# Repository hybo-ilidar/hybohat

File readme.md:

# Hybohat Development Board 

## Update R3

Correction was made for Arduino Nano module.
ESP32 module was adjusted for use with male pin header modules.

## Introduction

The Hybohat module was designed as a simple, passive way to interconnect
the User I/O connector of the iLidar to a variety of common development
boards.  These are:

* STM32F4 Discovery
* Arduino Uno & Leonardo
* STM32F429ZI Nucleo
* ESP32
* Raspberry Pi & Pi Zero
* Arduino Nano (and STM32F103 Nano form-factor)

## Concept

The board can be envisioned as a large cross-bar switch with each
dev board's I/O ports conected to a bus.  In case a development board
has multiple ports of the same time, the desired port is selected with 
jumpers in the three vertical columns labeled 

* `SPI SEL JUMPERS` (JP4NN1, JP4DD1)
* `I2C SEL JUMPERS` (JP2NN1, JP2DD1)
* `ASYNC SEL JUMPERS` (JP3NN1, JP3DD1, JP2EE1)

One end of this bus is connected to iLidar's User I/O
connector by the jumper block labeled: `I/O MODE SELECT (JP6)`
Note that only one mode can be operational at a time.

The other end of the bus is terminated in four connectors which can be
used to probe and monitor the I/O:

* `I2C` (J2)
* `SPI` (J3)
* `ASYNC` (J4)
* `TRIG` (J5)

## Development Boards

IMPORTANT: ONLY ONE DEVELOPMENT BOARD MAY BE CONNECTED AT ONE TIME

* Module A2, ESP32
  - XA2J2
  - XA2J3

* Module A3, Raspberry Pi & Pi Zero
  - XA3GPIO1

* Module A4, Arduino Nano
  - XA4J1 
  - XA4J2 

* Module A5, STM32F4 Discovery 
  - XA5P1
  - XA5P2

* Module A6, STM32F429ZI Nucleo Arduino Uno & Leonardo
  - XA6CN7
  - XA6CN8
  - XA6CN9
  - XA6CN10

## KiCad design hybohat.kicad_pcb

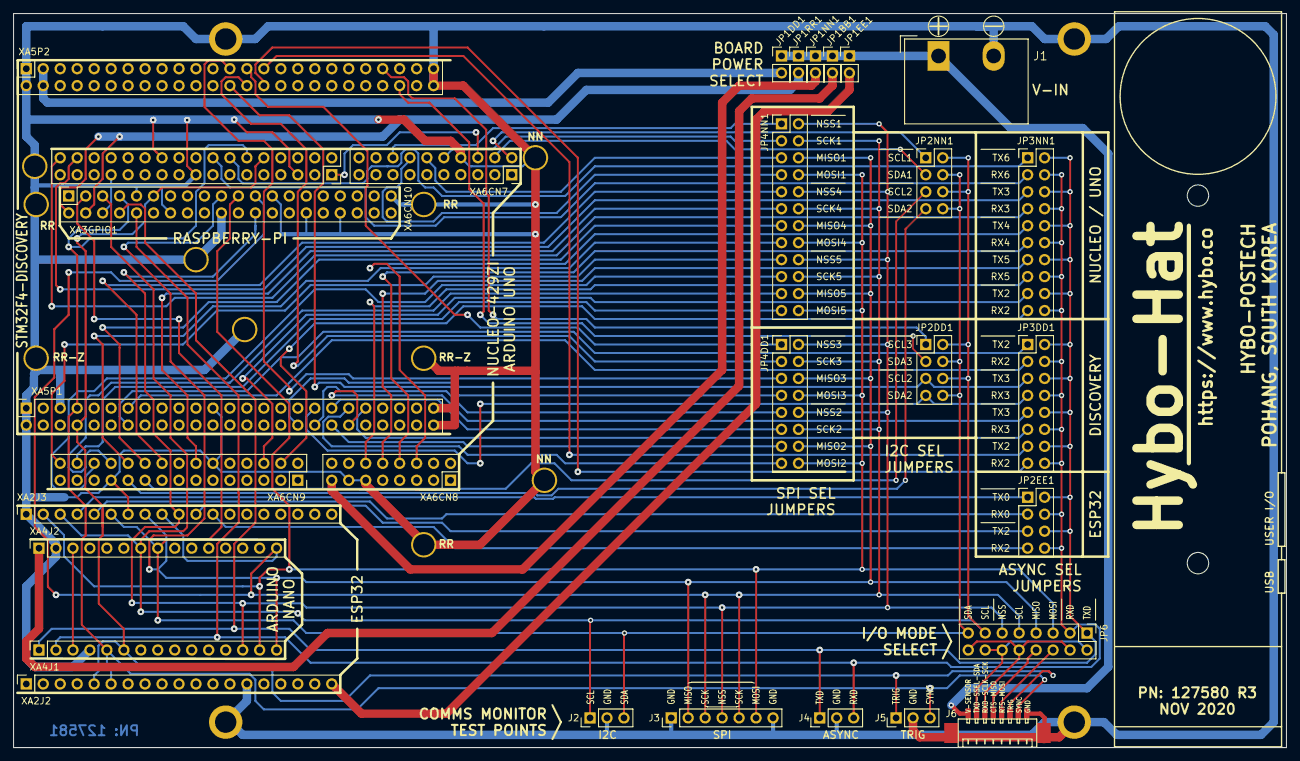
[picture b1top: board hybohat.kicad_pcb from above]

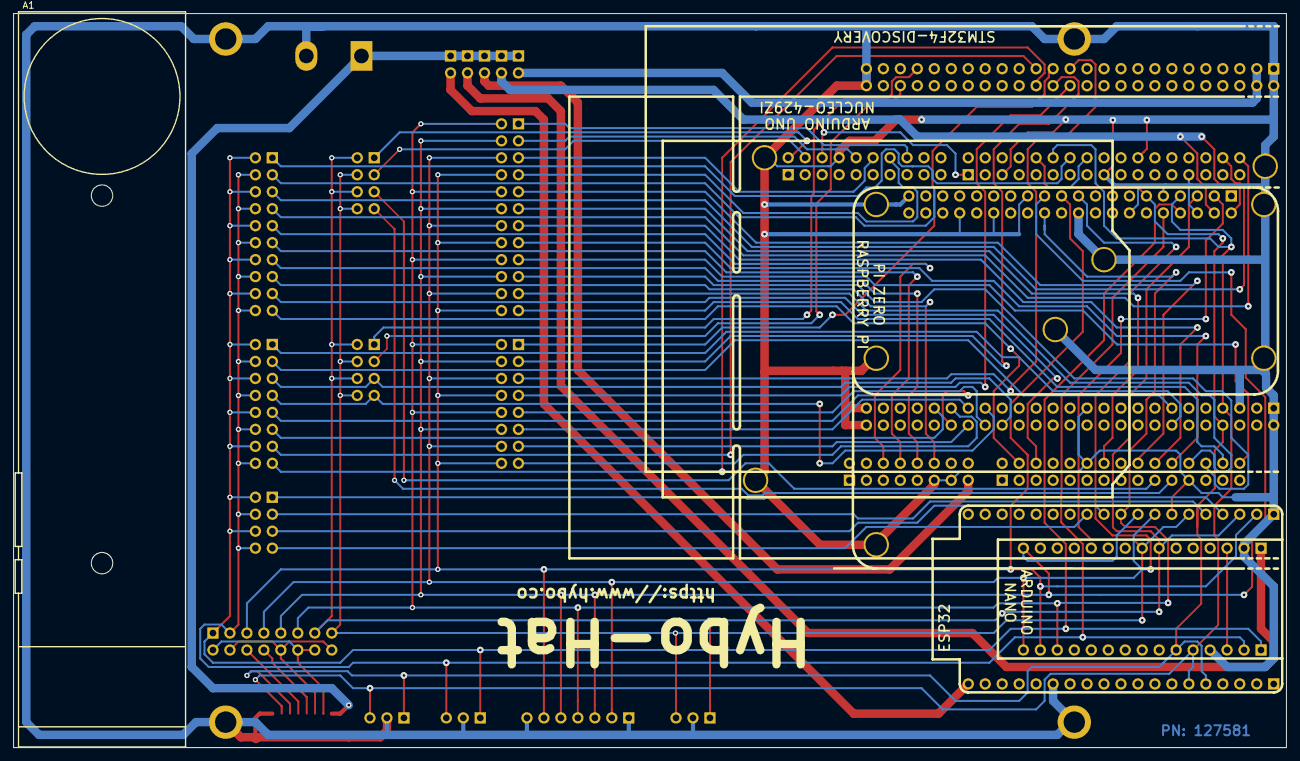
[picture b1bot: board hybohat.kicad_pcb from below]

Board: 2 copper layers, 190.5 x 109.9 mm, 45 parts (2 on the bottom side), 71 nets.

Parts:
A1: ASSY_SENSOR_LIDAR; iLidar
H1, H2, H3, H4: MountingHole_Pad; MountingHole_3.2mm_M3_Pad
J1: DC-PWR-IN; TerminalBlock_Molex_1x02_0.375
J2, J4, J5: IO_JACK_M03; Connector_PinHeader_2.54mm_PinHeader_1x03_P2.54mm_Vertical
J3: IO_JACK_M07; Connector_PinHeader_2.54mm_PinHeader_1x07_P2.54mm_Vertical
J6: CONN_1x8; USER_IO_CONN
JP1BB1: BB_PWR; Connector_PinHeader_2.54mm_PinHeader_1x02_P2.54mm_Vertical
JP1DD1: DD_PWR; Connector_PinHeader_2.54mm_PinHeader_1x02_P2.54mm_Vertical
JP1EE1: EE_PWR; Connector_PinHeader_2.54mm_PinHeader_1x02_P2.54mm_Vertical
JP1NN1: NN_PWR; Connector_PinHeader_2.54mm_PinHeader_1x02_P2.54mm_Vertical
JP1RR1: RR_PWR; Connector_PinHeader_2.54mm_PinHeader_1x02_P2.54mm_Vertical
JP2DD1: DD_I2C_SEL; Connector_PinHeader_2.54mm_PinHeader_2x04_P2.54mm_Vertical
JP2EE1: EE_ASYNC_SEL; Connector_PinHeader_2.54mm_PinHeader_2x04_P2.54mm_Vertical
JP2NN1: NN_I2C_SEL; Connector_PinHeader_2.54mm_PinHeader_2x04_P2.54mm_Vertical
JP3DD1: DD_ASYNC_SEL; Connector_PinHeader_2.54mm_PinHeader_2x08_P2.54mm_Vertical
JP3NN1: NN_ASYNC_SEL; Connector_PinHeader_2.54mm_PinHeader_2x10_P2.54mm_Vertical
JP4DD1: DD_SPI_SEL; Connector_PinHeader_2.54mm_PinHeader_2x08_P2.54mm_Vertical
JP4NN1: NN_SPI_SEL; Connector_PinHeader_2.54mm_PinHeader_2x12_P2.54mm_Vertical
JP6: IO_JACK_M2x08B; Connector_PinHeader_2.54mm_PinHeader_2x08_P2.54mm_Vertical
MH1, MH2, MH3, MH4, MH5, MH6, MH7, MH8, MH9, MH10: MountingHole_Pad; MountingHole_3.2mm_M3
XA2J2: EE_F1x19_J2; Connector_PinSocket_2.54mm_PinSocket_1x19_P2.54mm_Vertical
XA2J3: EE_F1x19_J3; Connector_PinSocket_2.54mm_PinSocket_1x19_P2.54mm_Vertical
XA3GPIO1: RR_F2x20_GPIO; Connector_PinSocket_2.54mm_PinSocket_2x20_P2.54mm_Vertical
XA4J1: BB_F1x15_J1; Connector_PinSocket_2.54mm_PinSocket_1x15_P2.54mm_Vertical
XA4J2: BB_F1x15_J2; Connector_PinSocket_2.54mm_PinSocket_1x15_P2.54mm_Vertical
XA5P1: DD_F2x25_P1; Connector_PinSocket_2.54mm_PinSocket_2x25_P2.54mm_Vertical
XA5P2: DD_F2x25_P2; Connector_PinSocket_2.54mm_PinSocket_2x25_P2.54mm_Vertical
XA6CN7: NN_M2x10_CN7; PinHeader_2x10_P2.54mm_Vertical_Mirrored
XA6CN8: NN_M2x8_CN8; PinHeader_2x08_P2.54mm_Vertical_Mirrored
XA6CN9: NN_M2x15_CN9; PinHeader_2x15_P2.54mm_Vertical_Mirrored
XA6CN10: NN_M2x17_CN10; PinHeader_2x17_P2.54mm_Vertical_Mirrored

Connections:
+Vin: J1.1, J6.1, JP1BB1.1, JP1DD1.1, JP1EE1.1, JP1NN1.1, JP1RR1.1
/ASYNC_RXD: J4.3, JP2EE1.4, JP2EE1.8, JP3DD1.4, JP3DD1.8, JP3DD1.12, JP3DD1.16, JP3NN1.4, JP3NN1.8, JP3NN1.12, JP3NN1.16, JP3NN1.20, JP6.3, XA3GPIO1.10, XA4J1.2
/ASYNC_TXD: J4.1, JP2EE1.2, JP2EE1.6, JP3DD1.2, JP3DD1.6, JP3DD1.10, JP3DD1.14, JP3NN1.2, JP3NN1.6, JP3NN1.10, JP3NN1.14, JP3NN1.18, JP6.1, XA3GPIO1.8, XA4J1.1
/BB_PB2_D10_NSS: J3.4, JP4DD1.2, JP4DD1.10, JP4NN1.2, JP4NN1.10, JP4NN1.18, JP6.11, XA2J3.10, XA3GPIO1.24, XA4J1.13
/BB_PB3_D11_MOSI: J3.6, JP4DD1.8, JP4DD1.16, JP4NN1.8, JP4NN1.16, JP4NN1.24, JP6.5, XA2J3.2, XA3GPIO1.21, XA4J1.14
/BB_PB4_D12_MISO: J3.2, JP4DD1.6, JP4DD1.14, JP4NN1.6, JP4NN1.14, JP4NN1.22, JP6.7, XA2J3.8, XA3GPIO1.19, XA4J1.15
/BB_PB5_D13_SCK: J3.3, J3.5, JP4DD1.4, JP4DD1.12, JP4NN1.4, JP4NN1.12, JP4NN1.20, JP6.9, XA2J3.9, XA3GPIO1.23, XA4J2.15
/BB_PC4_D18_ADC4_A4_SDA: J2.3, JP2DD1.4, JP2DD1.8, JP2NN1.4, JP2NN1.8, JP6.15, XA2J3.6, XA3GPIO1.3, XA4J2.8
/BB_PC5_D19_ADC5_A5_SCL: J2.1, JP2DD1.2, JP2DD1.6, JP2NN1.2, JP2NN1.6, JP6.13, XA2J3.3, XA3GPIO1.5, XA4J2.7
/BB_PC6_RESET: XA4J1.3, XA4J2.3
/BB_PD2_D2_INT0: J5.3, J6.7, XA2J2.6, XA3GPIO1.7, XA4J1.5, XA5P1.7, XA6CN10.12
/BB_PD3_D3_INT1: J5.1, J6.6, XA2J2.5, XA3GPIO1.11, XA4J1.6, XA5P1.8, XA6CN10.10
/BB_VIN: JP1BB1.2, XA4J2.1
/CTS_MISO: J6.4, JP6.8
/DD_5V: JP1DD1.2, XA5P2.3, XA5P2.4
/DD_MISO2: JP4DD1.13, XA5P1.38
/DD_MISO3: JP4DD1.5, XA5P2.25
/DD_MOSI2: JP4DD1.15, XA5P1.39
/DD_MOSI3: JP4DD1.7, XA5P2.26
/DD_NSS2: JP4DD1.9, XA5P1.36
/DD_NSS3_BB: JP4DD1.1, XA5P2.27
/DD_PA2_TX2: JP3DD1.1, XA5P1.14
/DD_PA3_RX2: JP3DD1.3, XA5P1.13
/DD_PA8_SCL3: JP2DD1.1, XA5P2.43
/DD_PB3_SCK1_SCK3: JP4DD1.3, XA5P2.28
/DD_PB10_SCK2_SCL2_TX3_MIC: JP2DD1.5, JP3DD1.5, XA5P1.34
/DD_PB11_SDA2_RX3: JP2DD1.7, JP3DD1.7, XA5P1.35
/DD_PB13_SCK2: JP4DD1.11, XA5P1.37
/DD_PC9_SDA3: JP2DD1.3, XA5P2.46
/DD_PD5_TX2: JP3DD1.13, XA5P2.29
/DD_PD6_RX2: JP3DD1.15, XA5P2.30
/DD_PD8_TX3: JP3DD1.9, XA5P1.40
/DD_PD9_RX3: JP3DD1.11, XA5P1.41
/EE_EXT_5V: JP1EE1.2, XA2J2.19
/EE_IO16_RXD2: JP2EE1.7, XA2J3.12
/EE_IO17_TXD2: JP2EE1.5, XA2J3.11
/EE_RXD0: JP2EE1.3, XA2J3.5
/EE_TXD0: JP2EE1.1, XA2J3.4
/NN_AREF: XA6CN7.6, XA6CN10.1
/NN_MISO1: JP4NN1.5, XA6CN7.12
/NN_MISO4: JP4NN1.13, XA6CN9.20
/NN_MISO5: JP4NN1.21, XA6CN9.24
/NN_MOSI1: JP4NN1.7, XA6CN7.14
/NN_MOSI4: JP4NN1.15, XA6CN9.22
/NN_MOSI5: JP4NN1.23, XA6CN9.28
/NN_NSS1: JP4NN1.1, XA6CN7.16
/NN_NSS4: JP4NN1.9, XA6CN9.18
/NN_PA5_D13_SCK1: JP4NN1.3, XA6CN7.10
/NN_PB8_SCL1: JP2NN1.1, XA6CN7.2
/NN_PB9_SDA1: JP2NN1.3, XA6CN7.4
/NN_PB10_SCL2_TX3: JP3NN1.5, XA6CN10.32
/NN_PB11_SDA2_RX3: JP3NN1.7, XA6CN10.34
/NN_PC10_TX3_TX4: JP3NN1.9, XA6CN8.6
/NN_PC11_RX3_RX4: JP3NN1.11, XA6CN8.8
/NN_PC12_TX5: JP3NN1.13, XA6CN8.10
/NN_PD2_RX5: JP3NN1.15, XA6CN8.12
/NN_PD5_TX2: JP3NN1.17, XA6CN9.6
/NN_PD6_RX2: JP3NN1.19, XA6CN9.4
/NN_PE2_SCK4: JP4NN1.11, XA6CN9.14
/NN_PF0_SDA2: JP2NN1.7, XA6CN9.21
/NN_PF1_SCL2: JP2NN1.5, XA6CN9.19
/NN_PF7_SCK5: JP4NN1.19, XA6CN9.26
/NN_PG1: JP4NN1.17, XA6CN9.30
/NN_PG9_D0_RX6: JP3NN1.3, XA6CN10.16
/NN_PG15_D1_TX6: JP3NN1.1, XA6CN10.14
/NN_VIN: JP1NN1.2, XA6CN8.15
/RR_5V: JP1RR1.2, XA3GPIO1.2, XA3GPIO1.4
/RTS_MOSI: J6.5, JP6.6
/RXD_SCLK_SCK: J6.3, JP6.4, JP6.10, JP6.16
/TXD_SSEL_SDA: J6.2, JP6.2, JP6.12, JP6.14
GND: H1.1, H2.1, H3.1, H4.1, J1.2, J2.2, J3.1, J3.7, J4.2, J5.2, J6.8, J6.9, J6.10, MH1.1, MH2.1, MH3.1, MH4.1, MH5.1, MH6.1, MH7.1, MH8.1, MH9.1, MH10.1, XA2J2.14, XA2J3.1, XA2J3.7, XA3GPIO1.6, XA3GPIO1.9, XA3GPIO1.14, XA3GPIO1.20, XA3GPIO1.25, XA3GPIO1.30, XA3GPIO1.34, XA3GPIO1.39, XA4J1.4, XA4J2.2, XA5P1.1, XA5P1.2, XA5P1.5, XA5P1.23, XA5P1.49, XA5P1.50, XA5P2.1, XA5P2.2, XA5P2.49, XA5P2.50, XA6CN7.8, XA6CN8.11, XA6CN8.13, XA6CN9.12, XA6CN9.23, XA6CN10.5, XA6CN10.17, XA6CN10.22, XA6CN10.27

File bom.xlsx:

HYBOHAT ASSEMBLY |  |  | DRAFT version, additional fill-in to be done
P/N 127580
43972
FN | Ref | Qty | Comm | Manufacturer | PartNumber | Value | Cmp name
1 | A1, | 1 | ASY | Hybo | 127290 | ASSY_SENSOR_LIDAR | ASSY_SENSOR_LIDAR |  | iLidar Sensor
2 | A2 | 1 |  |  |  |  |  |  | ESP32
3 | A3 |  |  |  |  |  |  |  | Raspberry Pi & Pi Zero
4 | A4 |  |  |  |  |  |  |  | Arduino Nano (and STM32F103 Nano form-factor)
5 | A5 |  |  |  |  |  |  |  | STM32F4 Discovery
6 | A6 |  |  |  |  |  |  |  | STM32F429ZI Nucleo, Arduino Uno & Leonardo
7 | J1, | 1 | CON | Molex | 387007502 | DC-PWR-IN | Screw_Terminal_01x02 |  | Connector, Barrier Strip, #6032, 2 posn, 0.325 in pitch | LCSC | C8450 | Digikey | WM13920-ND
8 | J6, | 1 | CON | Molex | 532610871 | CONN_1x8 | CONN_1x8 | M1x08 | Connector, Plug, Wafer Pico-Blade, SMD R/A, 8-posn, 1.25 mm pitch |  |  | Digikey | WM7626TR-ND
9 | J2, J4, J5, | 3 | CON |  |  | IO_JACK_M03 | IO_JACK_M03 | M1x03
10 | J3, | 1 | CON |  |  | IO_JACK_M07 | IO_JACK_M07 | M1x07
11 | JP1 | 1 | CON |  |  | PWR-SEL | IO_JACK_M2x01B | M2x10
12 | JP2DD1, | 1 | CON |  |  | DD_I2C_SEL | IO_JACK_M2x04B | M2x04
13 | JP2EE1, | 1 | CON |  |  | EE_ASYNC_SEL | IO_JACK_M2x04B | M2x04
14 | JP2NN1, | 1 | CON |  |  | NN_I2C_SEL | IO_JACK_M2x04B | M2x04
15 | JP3DD1, | 1 | CON |  |  | DD_ASYNC_SEL | IO_JACK_M2x08B | M2x08
16 | JP3NN1, | 1 | CON |  |  | NN_ASYNC_SEL | IO_JACK_M2x10B | M2x10
17 | JP4DD1, | 1 | CON |  |  | DD_SPI_SEL | IO_JACK_M2x08B | M2x08
18 | JP4NN1, | 1 | CON |  |  | NN_SPI_SEL | IO_JACK_M2x12B | M2x12
19 | JP6, | 1 | CON |  |  | IO_JACK_M2x08B | IO_JACK_M2x08B_SENSOR | M2x08
20 | XA2J2, | 1 | CON |  |  | EE_F1x19_J2 | IO_JACK_F19 | F1x19
21 | XA2J3, | 1 | CON |  |  | EE_F1x19_J3 | IO_JACK_F19 | F1x19
22 | XA3GPIO1, | 1 | CON |  |  | RR_F2x20_GPIO | IO_JACK_F2x20B | F2x20
23 | XA4J1, | 1 | CON |  |  | BB_F1x15_J1 | IO_JACK_F15 | F1x15
24 | XA4J2, | 1 | CON |  |  | BB_F1x15_J2 | IO_JACK_F15 | F1x15
25 | XA5P1, | 1 | CON |  |  | DD_F2x25_P1 | IO_JACK_F2x25 | F2x25
26 | XA5P2, | 1 | CON |  |  | DD_F2x25_P2 | IO_JACK_F2x25 | F2x25
27 | XA6CN7, | 1 | CON |  |  | NN_M2x10_CN7 | IO_JACK_M2x10B_NN429ZI | M2x10
28 | XA6CN8, | 1 | CON |  |  | NN_M2x8_CN8 | IO_JACK_M2x08B_NN429ZI | M2x08
29 | XA6CN9, | 1 | CON |  |  | NN_M2x15_CN9 | IO_JACK_M2x15B_NN429ZI | M2x15
30 | XA6CN10, | 1 | CON |  |  | NN_M2x17_CN10 | IO_JACK_M2x17B_NN429ZI | M2x17
31 |  | 1 | PCB | Hybo | 127581 |  |  |  | Printed circuit board, Hybohat

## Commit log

2020-05-21 Initial public release
2020-05-21 fixed image display in readme
2020-05-21 really fixed the images this time
2020-05-21 oops, image is TOO big
2020-11-12 updates for rev3, fixed Arduino Nano
2020-11-12 changed ESP32 module to have male pins
2020-11-12 Updated BOM with to-buy details
2020-11-16 added kit quantities to BOM
